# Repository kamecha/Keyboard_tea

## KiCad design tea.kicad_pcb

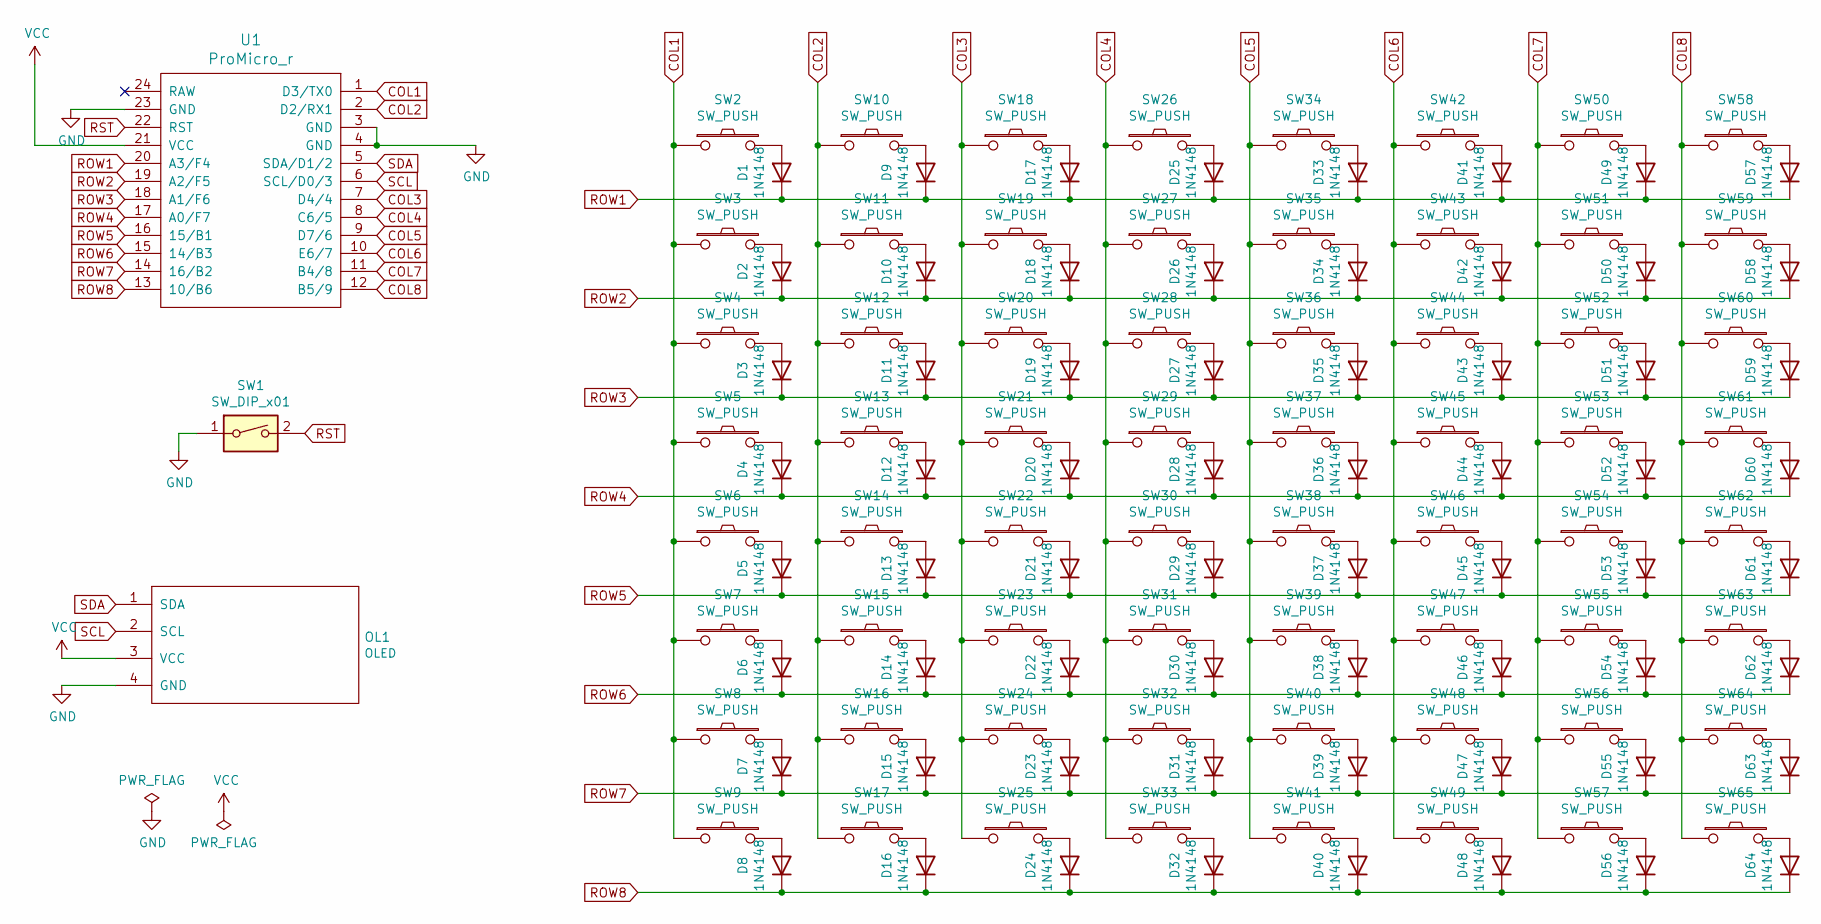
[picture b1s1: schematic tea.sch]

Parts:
D1, D2, D3, D4, D5, D6, D7, D8, D9, D10, D11, D12, D13, D14, D15, D16, D17, D18, D19, D20, D21, D22, D23, D24, D25, D26, D27, D28, D29, D30, D31, D32, D33, D34, D35, D36, D37, D38, D39, D40, D41, D42, D43, D44, D45, D46, D47, D48, D49, D50, D51, D52, D53, D54, D55, D56, D57, D58, D59, D60, D61, D62, D63, D64: 1N4148; D3_TH_SMD_v2
OL1: OLED; OLED_v2
SW1: SW_DIP_x01; ResetSW_1side
SW2, SW3, SW4, SW5, SW6, SW7, SW8, SW9, SW10, SW11, SW12, SW13, SW14, SW15, SW16, SW17, SW18, SW19, SW20, SW21, SW22, SW23, SW24, SW25, SW26, SW27, SW28, SW29, SW30, SW31, SW32, SW33, SW34, SW35, SW36, SW37, SW38, SW39, SW40, SW41, SW42, SW43, SW44, SW45, SW46, SW47, SW50: SW_PUSH; SW_Cherry_MX_1.00u_PCB
SW48: SW_PUSH; SW_Cherry_MX_2.00u_PCB
SW49, SW51, SW54: SW_PUSH; SW_Cherry_MX_1.50u_PCB
SW52, SW63: SW_PUSH; SW_Cherry_MX_1.75u_PCB
SW53, SW65: SW_PUSH; SW_Cherry_MX_2.25u_PCB
SW55, SW56, SW57, SW59, SW60, SW61, SW62: SW_PUSH; SW_Cherry_MX_1.25u_PCB
SW58: SW_PUSH; SW_Cherry_MX_3.00u_PCB
SW64: SW_PUSH; SW_Cherry_MX_2.75u_PCB
U1: ProMicro_r; ProMicro_v3

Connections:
COL1: SW2.1, SW3.1, SW4.1, SW5.1, SW6.1, SW7.1, SW8.1, SW9.1, U1.1 (D3/TX0)
COL2: SW10.1, SW11.1, SW12.1, SW13.1, SW14.1, SW15.1, SW16.1, SW17.1, U1.2 (D2/RX1)
COL3: SW18.1, SW19.1, SW20.1, SW21.1, SW22.1, SW23.1, SW24.1, SW25.1, U1.7 (D4/4)
COL4: SW26.1, SW27.1, SW28.1, SW29.1, SW30.1, SW31.1, SW32.1, SW33.1, U1.8 (C6/5)
COL5: SW34.1, SW35.1, SW36.1, SW37.1, SW38.1, SW39.1, SW40.1, SW41.1, U1.9 (D7/6)
COL6: SW42.1, SW43.1, SW44.1, SW45.1, SW46.1, SW47.1, SW48.1, SW49.1, U1.10 (E6/7)
COL7: SW50.1, SW51.1, SW52.1, SW53.1, SW54.1, SW55.1, SW56.1, SW57.1, U1.11 (B4/8)
COL8: SW58.1, SW59.1, SW60.1, SW61.1, SW62.1, SW63.1, SW64.1, SW65.1, U1.12 (B5/9)
GND: OL1.4 (GND), SW1.1, U1.3 (GND), U1.4 (GND), U1.23 (GND)
unnamed: D1.2 (A), SW2.2
unnamed: D2.2 (A), SW3.2
unnamed: D3.2 (A), SW4.2
unnamed: D4.2 (A), SW5.2
unnamed: D5.2 (A), SW6.2
unnamed: D6.2 (A), SW7.2
unnamed: D7.2 (A), SW8.2
unnamed: D8.2 (A), SW9.2
unnamed: D9.2 (A), SW10.2
unnamed: D10.2 (A), SW11.2
unnamed: D11.2 (A), SW12.2
unnamed: D12.2 (A), SW13.2
unnamed: D13.2 (A), SW14.2
unnamed: D14.2 (A), SW15.2
unnamed: D15.2 (A), SW16.2
unnamed: D16.2 (A), SW17.2
unnamed: D17.2 (A), SW18.2
unnamed: D18.2 (A), SW19.2
unnamed: D19.2 (A), SW20.2
unnamed: D20.2 (A), SW21.2
unnamed: D21.2 (A), SW22.2
unnamed: D22.2 (A), SW23.2
unnamed: D23.2 (A), SW24.2
unnamed: D24.2 (A), SW25.2
unnamed: D25.2 (A), SW26.2
unnamed: D26.2 (A), SW27.2
unnamed: D27.2 (A), SW28.2
unnamed: D28.2 (A), SW29.2
unnamed: D29.2 (A), SW30.2
unnamed: D30.2 (A), SW31.2
unnamed: D31.2 (A), SW32.2
unnamed: D32.2 (A), SW33.2
unnamed: D33.2 (A), SW34.2
unnamed: D34.2 (A), SW35.2
unnamed: D35.2 (A), SW36.2
unnamed: D36.2 (A), SW37.2
unnamed: D37.2 (A), SW38.2
unnamed: D38.2 (A), SW39.2
unnamed: D39.2 (A), SW40.2
unnamed: D40.2 (A), SW41.2
unnamed: D41.2 (A), SW42.2
unnamed: D42.2 (A), SW43.2
unnamed: D43.2 (A), SW44.2
unnamed: D44.2 (A), SW45.2
unnamed: D45.2 (A), SW46.2
unnamed: D46.2 (A), SW47.2
unnamed: D47.2 (A), SW48.2
unnamed: D48.2 (A), SW49.2
unnamed: D49.2 (A), SW50.2
unnamed: D50.2 (A), SW51.2
unnamed: D51.2 (A), SW52.2
unnamed: D52.2 (A), SW53.2
unnamed: D53.2 (A), SW54.2
unnamed: D54.2 (A), SW55.2
unnamed: D55.2 (A), SW56.2
unnamed: D56.2 (A), SW57.2
unnamed: D57.2 (A), SW58.2
unnamed: D58.2 (A), SW59.2
unnamed: D59.2 (A), SW60.2
unnamed: D60.2 (A), SW61.2
unnamed: D61.2 (A), SW62.2
unnamed: D62.2 (A), SW63.2
unnamed: D63.2 (A), SW64.2
unnamed: D64.2 (A), SW65.2
ROW1: D1.1 (K), D9.1 (K), D17.1 (K), D25.1 (K), D33.1 (K), D41.1 (K), D49.1 (K), D57.1 (K), U1.20 (A3/F4)
ROW2: D2.1 (K), D10.1 (K), D18.1 (K), D26.1 (K), D34.1 (K), D42.1 (K), D50.1 (K), D58.1 (K), U1.19 (A2/F5)
ROW3: D3.1 (K), D11.1 (K), D19.1 (K), D27.1 (K), D35.1 (K), D43.1 (K), D51.1 (K), D59.1 (K), U1.18 (A1/F6)
ROW4: D4.1 (K), D12.1 (K), D20.1 (K), D28.1 (K), D36.1 (K), D44.1 (K), D52.1 (K), D60.1 (K), U1.17 (A0/F7)
ROW5: D5.1 (K), D13.1 (K), D21.1 (K), D29.1 (K), D37.1 (K), D45.1 (K), D53.1 (K), D61.1 (K), U1.16 (15/B1)
ROW6: D6.1 (K), D14.1 (K), D22.1 (K), D30.1 (K), D38.1 (K), D46.1 (K), D54.1 (K), D62.1 (K), U1.15 (14/B3)
ROW7: D7.1 (K), D15.1 (K), D23.1 (K), D31.1 (K), D39.1 (K), D47.1 (K), D55.1 (K), D63.1 (K), U1.14 (16/B2)
ROW8: D8.1 (K), D16.1 (K), D24.1 (K), D32.1 (K), D40.1 (K), D48.1 (K), D56.1 (K), D64.1 (K), U1.13 (10/B6)
RST: SW1.2, U1.22 (RST)
SCL: OL1.2 (SCL), U1.6 (SCL/D0/3)
SDA: OL1.1 (SDA), U1.5 (SDA/D1/2)
VCC: OL1.3 (VCC), U1.21 (VCC)

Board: 2 copper layers, 131 parts (9 on the bottom side), 85 nets, no tracks yet.
